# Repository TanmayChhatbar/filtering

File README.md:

# Filtering Concepts PCB

This repository contains resources for a PCB project designed to help students understand basic filtering concepts in electronics.

https://github.com/user-attachments/assets/0b66fcd6-6c55-42dc-a5e1-664c0480170c

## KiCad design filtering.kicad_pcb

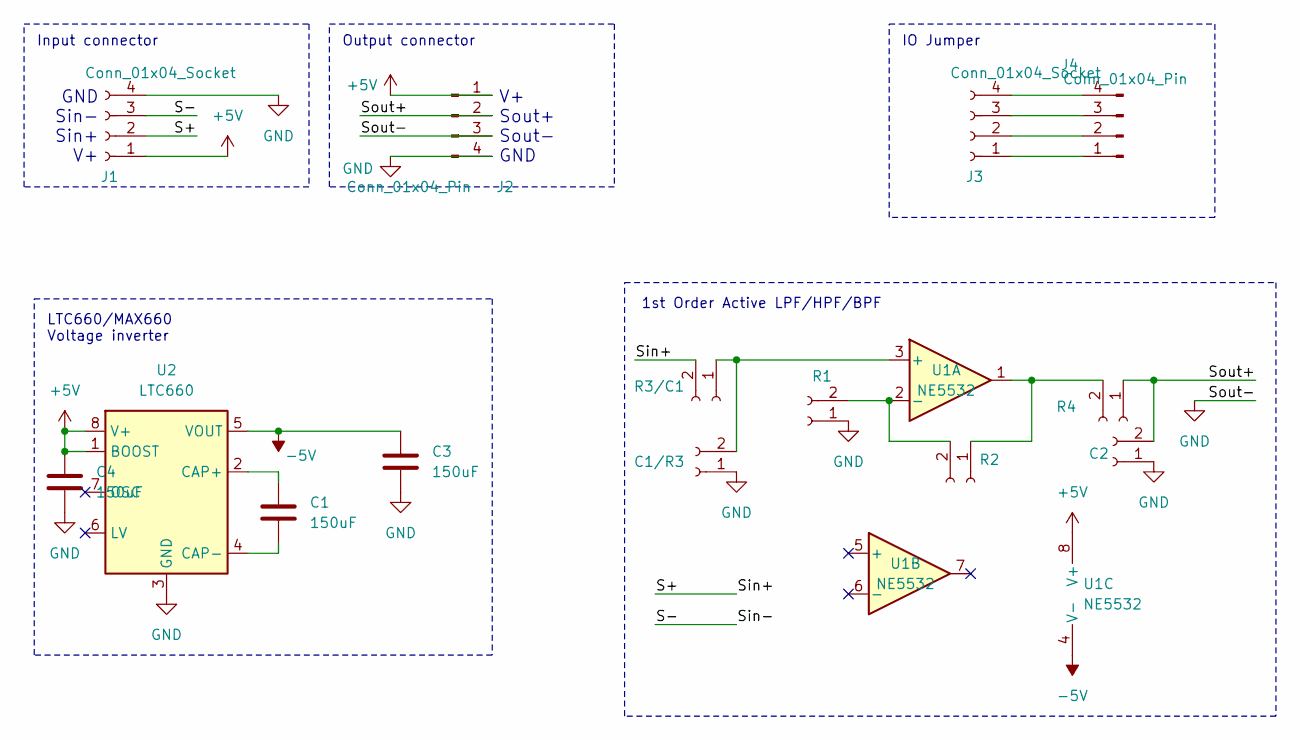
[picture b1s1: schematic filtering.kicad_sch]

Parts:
C1, C3, C4: 150uF; C_1206_3216Metric_Pad1.33x1.80mm_HandSolder
C1/R3, C2: Conn_01x02_Socket; PinSocket_1x02_P2.54mm_Vertical
J1, J3: Conn_01x04_Socket; PinSocket_1x04_P2.54mm_Vertical
J2, J4: Conn_01x04_Pin; PinHeader_1x04_P2.54mm_Vertical
R1, R2, R3/C1, R4: Conn_01x02_Socket; PinSocket_1x02_P2.54mm_Vertical
U1: NE5532; SOIC-8_3.9x4.9mm_P1.27mm
U2: LTC660; SOIC-8_3.9x4.9mm_P1.27mm

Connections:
+5V: C4.1, J1.1, J2.1, U1.8 (V+), U2.1 (BOOST), U2.8 (V+)
-5V: C3.1, U1.4 (V-), U2.5 (VOUT)
/S+: J1.2, R3/C1.2
/S-: J1.3
/Sout+: C2.2, J2.2, R4.1
GND: C1/R3.1, C2.1, C3.2, C4.2, J1.4, J2.3, J2.4, R1.1, U2.3 (GND)
unnamed: C1/R3.2, R3/C1.1, U1.3 (+)
unnamed: J3.1, J4.1
unnamed: J3.2, J4.2
unnamed: J3.3, J4.3
unnamed: J3.4, J4.4
unnamed: R1.2, R2.2, U1.2 (-)
unnamed: R2.1, R4.2, U1.1
unnamed: C1.1, U2.2 (CAP+)
unnamed: C1.2, U2.4 (CAP-)

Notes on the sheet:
V+ Sout+ Sout- GND
Output connector
Input connector
GND Sin- Sin+ V+
1st Order Active LPF/HPF/BPF
IO Jumper
LTC660/MAX660 Voltage inverter

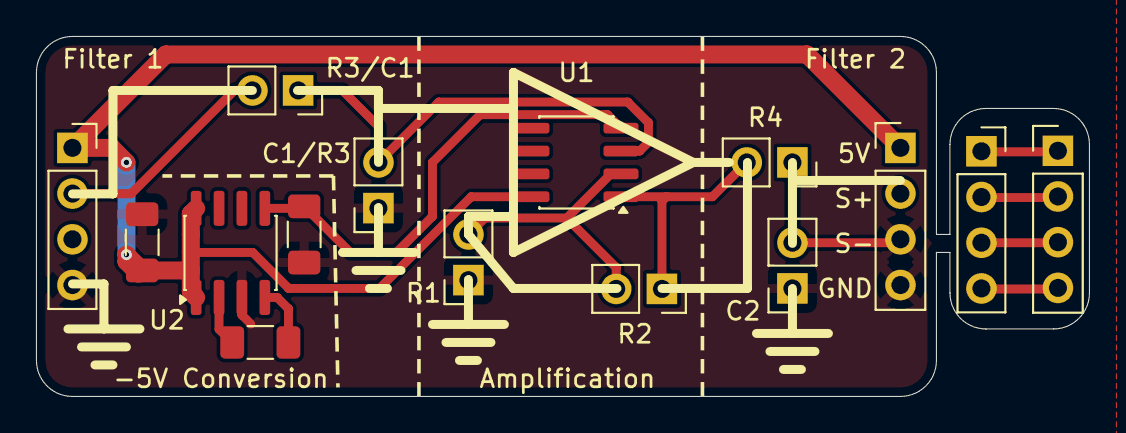
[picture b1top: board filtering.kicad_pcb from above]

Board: 2 copper layers, 58.5 x 20.0 mm, 15 parts (0 on the bottom side), 14 nets.

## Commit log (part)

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2026-01-22 init
2026-01-22 add readme
2026-01-22 pcb update to spread out components more evenly
2026-01-22 better spacing
2026-03-03 add jumper connector
